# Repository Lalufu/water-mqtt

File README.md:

# Water-MQTT gateway

This is a simple application that reads GPIO pin changes, and interprets
these as events coming from a water meter. It keeps track of the current
counter value and sends it to an MQTT gateway.

The application has no sense of the scale that the water meter operates
on, all it does is increase a counter by 1 every time the GPIO pin
changes state to low. It's up to the user to interpret the number properly.

This project uses the kernel [gpiod bindings](https://git.kernel.org/pub/scm/libs/libgpiod/libgpiod.git/)
to communicate with the GPIO subsystem. This library is a bit weird in the
sense that it is not available via pypi, but is very likely provided
by your OS.
There was a significant API change from 1.6.x versions to 2.x. This
project requires 2.x, although commits up to c6a48b189 will run on 1.6.x.

All other dependencies can be installed from pypi.

## Installation

Installation via pip into a venv is possible with `pip install .` from
the git checkout root, or via `pip install git+https://github.com/Lalufu/water-mqtt`.
This will also create the executable scripts in the `bin` dir of the venv.

In case you want to do things manually, the main entry point into
the program is `water_mqtt/cli.py:p1_mqtt()`.

## Development

This project uses [Poetry](https://python-poetry.org/) for dependency
management, and it's probably easiest to use this, Executing `poetry install 
` followed by `poetry run water-mqtt` from the git checkout root should
set up a venv, install the required dependencies into a venv and run
the main program.

## Running

`--config`
: Specify a configuration file to load. See the section `Configuration file`
  for details on the syntax. Command line options given in addition to the
  config file override settings in the config file.

`--mqtt-host`
: The MQTT host name to connect to. This is a required parameter.

  Config file: Section `general`, `mqtt-host`

`--mqtt-port`
: The MQTT port number to connect to. Defaults to 1883.

  Config file: Section `general`, `mqtt-port`

`--buffer-size`
: The size of the buffer (in number of measurements) that can be locally
  saved when the MQTT server is unavailable. The buffer is not persistent,
  and will be lost when the program exits. Defaults to 100000.

  Config file: Section `general`, `buffer-size`

`--mqtt-topic`
: The MQTT topic to publish the information to. This is a string that is put
  through python formatting, and can contain references to the variable `serial`.
  `serial` will contain the serial number of the meter, which
  can be set through the `--serial` command line option.
  The default is `water-mqtt/tele/%(serial)s/SENSOR`.

  Config file: Section `general`, `mqtt-topic`

`--mqtt-client-id`
: The client identifier used when connecting to the MQTT gateway. This needs
  to be unique for all clients connecting to the same gateway, only one
  client can be connected with the same name at a time. The default is
  `water-mqtt-gateway`.

  Config file: Section `general`, `mqtt-client-id`

`--gpiochip`
: The device file of the GPIO interface to use

  Config file: Section `general`, `gpiochip`

`--line`
: The GPIO line to use on the GPIO interface

  Config file: Section `general`, `line`

`--serial`
: The serial number of the water meter. Can be used as a variable in the
  `--mqtt-topic` option, and is also added to every MQTT message

  Config file: Section `general`, `serial`

`--http-host`
: Hostname for the built-in HTTP server (see below) to listen on.
  The default is `localhost`, and changing this is not recommended.

  Config file: Section `general`, `http-host`

`--http-port`
: Port for the built-in HTTP server (see below) to listen on.
  The default is `5000`.

  Config file: Section `general`, `http-port`

`--counter-file`
: File to use as storage for the counter value. The application will
  read this file on startup to initialize the counter, and will write the
  current value every 60 seconds, if the value has changed since the
  last write, and on application shutdown. Not being able to write to this
  file is not fatal.

  Config file: Section `general`, `counter-file`

## Configuration file
The program supports a configuration file to define behaviour. The
configuration file is in .ini file syntax, and can contain multiple sections.
The `[general]` section contains settings that define overall program
behaviour.

### Example configuration file

```
[general]
mqtt-client-id = water-gateway-01
mqtt-host = mqtt.example.com
gpiochip = /dev/gpiochip0
line = 18

```
## Data pushed to MQTT

The application pushes data to MQTT

- when the counter changes
- every 60 seconds if the counter does not change

Each push contains the following fields:

- `water_mqtt_timestamp`: The current UNIX timestamp, in milliseconds
- `counter`: The current counter value
- `debounced`: The number of GPIO events that were debounced
- `serial`: The serial number of the meter, as given through the `--serial`
  CLI option

## HTTP server

The application runs a simple HTTP server to allow setting the counter value.
The HTTP server listens on `localhost:5000` per default, and exposes two
endpoints.

To set the counter to `12345` using `curl`:

`curl -XPOST -d 12345 http://localhost:5000/counter/set`

On success, the endpoint returns the string `OK`.

To get the counter value using `curl`:

`curl http://localhost:5000/counter/get`

On success, the endpoint returns the current counter value.

## Counter value and startup

The application assumes that 0 is not a valid counter value, and will wait on
startup until the value is changed. This can be done through two mechanisms:

- Read a counter value from the file specified with the `--counter-file` CLI
  option
- Have the counter value set through the HTTP interface

Once either of these happen the application will start listening for GPIO
events and send data to MQTT.

## KiCAD project

The repository contains a [KiCad](https://www.kicad.org) project for a PCB
to connect the sensor to a Raspberry Pi in the `kicad` folder.

If all you're interested in is having a PCB made, take all `*.gbr`, `*.gbrjob`
and `*.drl` files, add them to a zip, and upload this to the PCB manufacturer
of your choice.

### Configuration

When using this PCB on a Raspberry Pi, use `--gpiochip=/dev/gpiochip0` and
`--line=18`.

### Components

The following components must be added to the PCB for it to work:

- `R1`, a 330 ohm resistor. This is the current limiting resistor for the LED
in `U1`.
- `R2`, a 5K1 ohm resistor. This is the pull-down resistor for the GPIO input
pin.
- `U1`, a 4N2x or 4N3x optocoupler (whatever you have or can get will be fine)
- `J2`, a 2x06 2.54mm pin socket. This connects to the GPIO connector of the
Raspberry Pi.

Note that `J2` goes onto the bottom side of the board, all other components
go to the top side.

The following components are optional.

- `J1`, a 1x03 2.54mm pin header. This connects to the sensor.
- `R3`, a pull up resistor for the GPIO input pin. Populate this if you don't
want to use the internal pullup resistor of the Raspberry Pi. I assume that if you
want this you know what you're doing, and you'll know how to size this. `R2`
might also have to be changed to fit.
- `C1`, a debouncing capacitor. The circuit should work fine without one. Size
this according to the pull-up and pull-down resistors on the GPIO input pin
to get a useful time constant. For the values given above, 100nF or 1uF should
be just fine. The specific type of capacitor does not matter much, both
polarized and non-polarized are fine.
- `J3`, a 1x03 2.54mm pin header. This is for breaking out debug signals,
should you want to hook an oscilloscope to the circuit.

### Sensor
The sensor is a LJ12A3-4-Z/BX metal proximity sensor. Multiple models of this
exist, pretty much any of them should work (both normally closed and normally open).

The `J1` jumper provides 5V (`BN`, brown wire), GND (`BL`, blue wire) and an
input pin (`BK`, black wire). It's expected that the sensor switches the input
pin between 5V and GND, depending on the sensor state.

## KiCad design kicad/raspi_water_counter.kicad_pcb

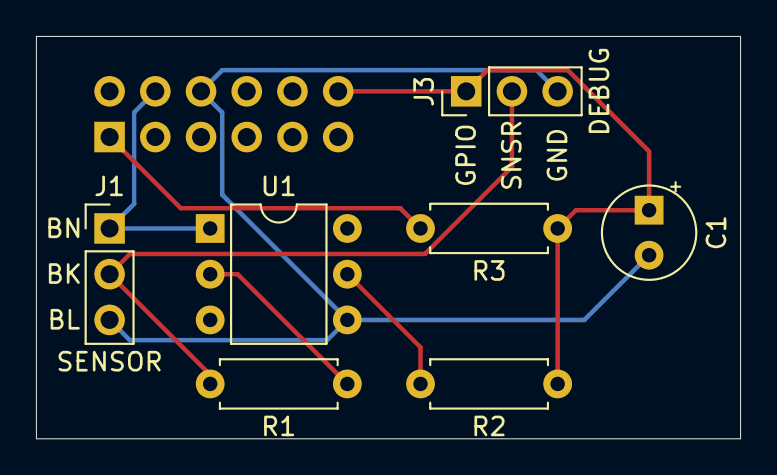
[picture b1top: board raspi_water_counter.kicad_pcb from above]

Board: 2 copper layers, 39.1 x 22.4 mm, 8 parts (1 on the bottom side), 7 nets.

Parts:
C1: 100nF; CP_Radial_Tantal_D5.0mm_P2.50mm
J1: SENSOR; PinHeader_1x03_P2.54mm_Vertical
J2: Raspi GPIO; PinSocket_2x06_P2.54mm_Vertical
J3: DEBUG; PinHeader_1x03_P2.54mm_Vertical
R1: 330; R_Axial_DIN0207_L6.3mm_D2.5mm_P7.62mm_Horizontal
R2: 5K1; R_Axial_DIN0207_L6.3mm_D2.5mm_P7.62mm_Horizontal
R3: R; R_Axial_DIN0207_L6.3mm_D2.5mm_P7.62mm_Horizontal
U1: 4N35; DIP-6_W7.62mm

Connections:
+3V3: J2.1, R3.2
+5V: J1.1, J2.4, U1.1
D1: C1.1, J2.12, J3.1, R2.1, R3.1
D2: J1.2, J3.2, R1.2
GND: C1.2, J1.3, J2.6, J3.3, U1.4
unnamed: R1.1, U1.2
unnamed: R2.2, U1.5

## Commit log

2021-12-20 water_mqtt.cli: Defer running until counter is non 0
2021-12-20 water_gpio.gpio: Add serial number to MQTT message
2021-12-20 water_mqtt.cli: Handle gpiochip and line from config file
2021-12-20 water_mqtt.cli: Handle writing counter file better
2021-12-20 water_mqtt.cli: Read "line" parameter as int from config
2021-12-20 water_mqtt.gpio: Make sure to send an event at least every 60 seconds
2021-12-21 water_mqtt.cli: Fix mode for temporary file
2021-12-30 water_mqtt.cli: Turn off time stamps in log messages when running under systemd
2021-12-31 water_mqtt.gpio: Fix formatting of counter change log messages
2021-12-31 water_mqtt.http: Add newline to messages returned from API, read host/port from config
2021-12-31 Rewrite README.md
2021-12-31 water_mqtt.http: Fix typo in bind config
2022-02-01 water_mqtt.http: Add support for /counter/get endpoint
2022-05-01 README.md: Update installation/development instructions
2022-05-01 Add kicad files for Raspberry Pi module
2022-05-02 README.md: Add description of Kicad project
2022-05-02 README.md: Clarify configuration when using the included PCB
2022-12-15 Handle unexpected death of the MQTT thread
2022-12-15 Bump version to 0.1.1
2022-12-15 Update minimum python version to 3.7.2, update dev tools versions
2022-12-15 Add configuration for black, isort, flake8, pylint
2022-12-15 Make pylint/flake8 clean
2022-12-23 Add +python-lsp-server as dev dependency
2024-02-13 Update project config
    Update project dependencies:
    - Minimal python version
    - Development dependencies
    - Requiring system packages (for libgpiod)
